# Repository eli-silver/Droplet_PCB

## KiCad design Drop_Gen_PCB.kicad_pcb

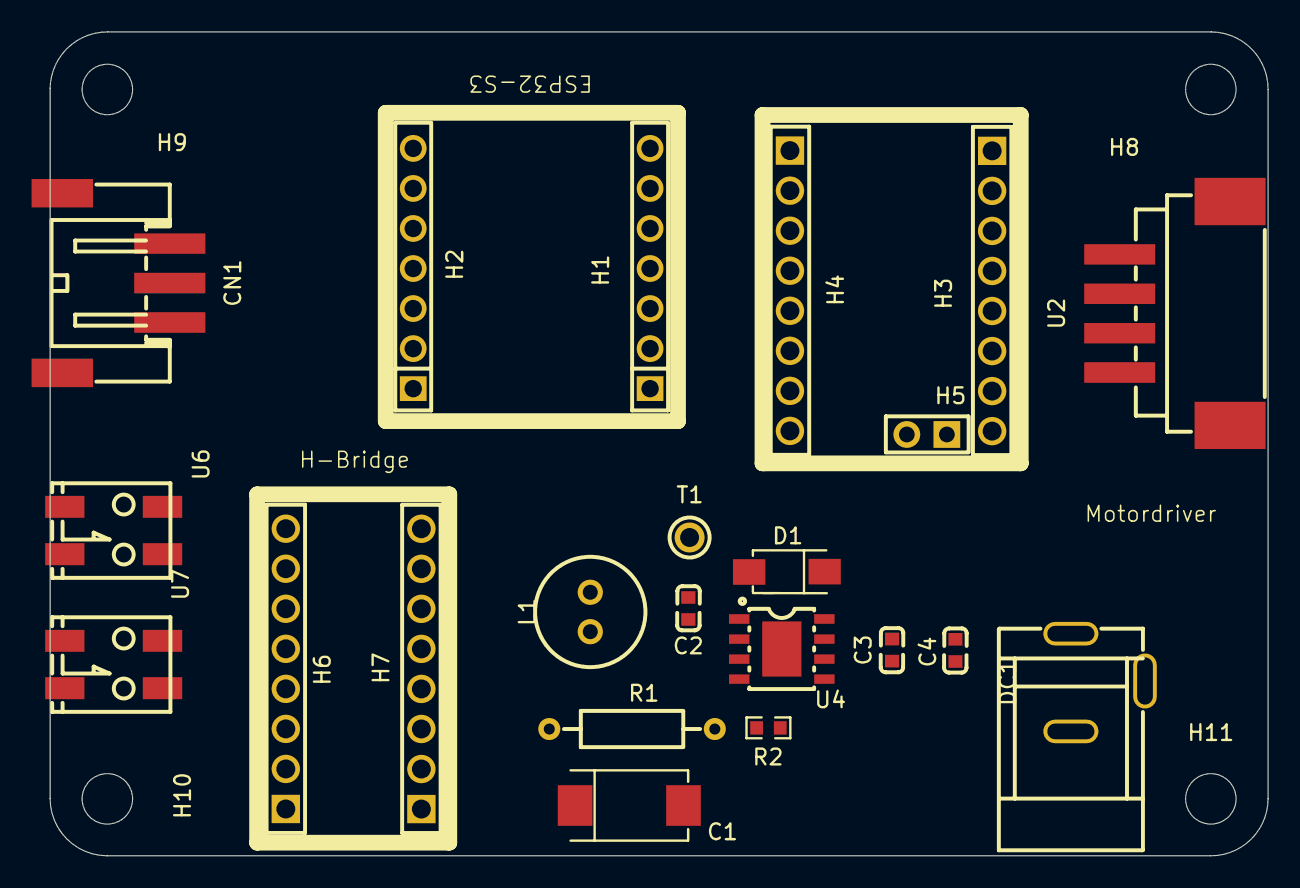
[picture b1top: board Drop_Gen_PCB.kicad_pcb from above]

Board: 2 copper layers, 77.3 x 52.3 mm, 26 parts (0 on the bottom side), 13 nets, no tracks yet.

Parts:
C1: 220uF; CAP-SMD_L7.3-W4.3-FD
C2: 10nF; C0603
C3, C4: 4.7uF; C0603
CN1: S3B-XH-SM4-TB (LF)(SN); CONN-TH_S3B-XH-SM4-TB-LF-SN
D1: B340A_C3018525; SMA_L4.3-W2.6-LS5.0-RD
DC1: Barrel Jack; DC-IN-TH_DC-470-2.1GP
H1, H2: PM254V-11-07-H85; HDR-TH_7P-P2.54-V-F
H3, H4, H6, H7: Header-Female-2.54_1x8; HDR-TH_8P-P2.54-V-F-1
H5: Header-Female-2.54_1x2; HDR-TH_2P-P2.54-V-F
H8, H9, H10, H11: MountingHole; MountingHole_3.2mm_M3
L1: 22uH; IND-TH_BD7.0-P2.50-D0.7
R1: 10KΩ; RES-TH_BD2.3-L6.5-P10.50-D0.5
R2: 3.24kΩ; R0603
T1: test_point; TEST-TH_BD2.54-P1.4_RED
U2: motor_header; CONN-SMD_S4B-XH-SM4-TB-LF-SN
U4: TPS5430DDAR; ESOP-8_L4.9-W3.9-P1.27-LS6.0-TL-EP
U6: Terminal Block Camera; CONN-SMD_2059-302
U7: TB Piezo; CONN-SMD_2059-302

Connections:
+5V: C1.1, H1.7, H3.2, H3.8, H4.7, H6.1, L1.1, R1.1
+30V: C3.2, C4.2, CN1.3, DC1.1, H7.8, U4.7 (VIN)
/Boot: C2.1, C2.2, D1.1 (K), L1.2, T1.1, U4.1 (BOOT), U4.8 (PH)
/Header: H2.3, H2.4
/Signal: CN1.1, H2.5
GND: C1.2, C3.1, C4.1, CN1.2, D1.2 (A), DC1.2, DC1.3, H1.6, H3.1, H3.7, H4.8, H6.4, H6.5, H7.4, H7.5, R2.2, U4.4 (VSENSE), U4.6 (GND), U4.9 (PowerPAD), U6.1
unnamed: CN1.4, CN1.5
unnamed: H3.3, U2.4
unnamed: H3.4, U2.3
unnamed: H3.5, U2.2
unnamed: H3.6, U2.1
unnamed: R1.2, R2.1
unnamed: U2.5, U2.6

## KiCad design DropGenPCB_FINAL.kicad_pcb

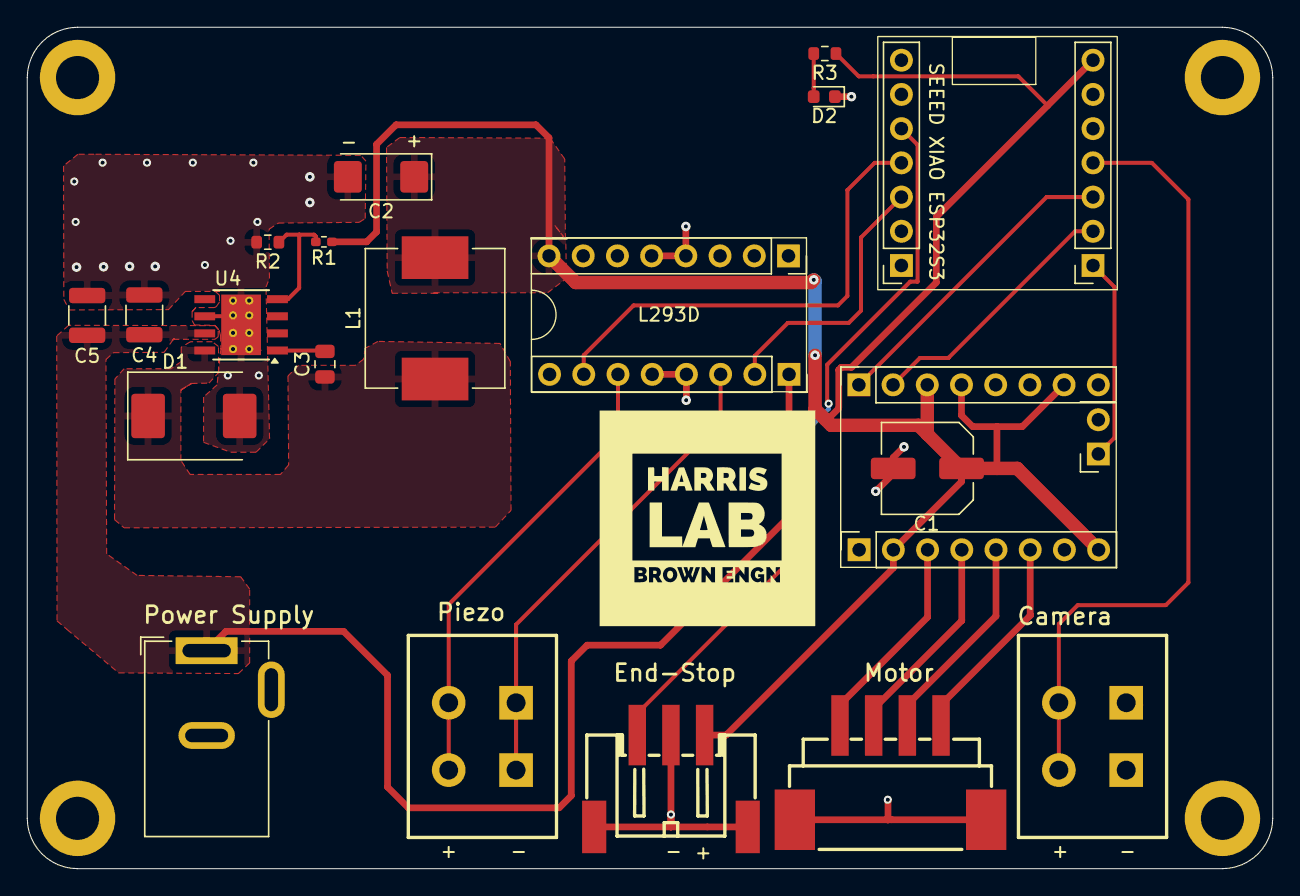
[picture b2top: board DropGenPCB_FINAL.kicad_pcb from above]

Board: 2 copper layers, 92.5 x 62.5 mm, 24 parts (0 on the bottom side), 20 nets.

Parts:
C1: 100uF; C_Elec_6.3x7.7
C2: 220uF; CP_EIA-6032-15_Kemet-U
C3: 10nF; C_0805_2012Metric
C4, C5: 4.7uF; C_1210_3225Metric
D1: B340A_C3018525; D_SMC
D2: LED; LED_0603_1608Metric
H1, H2, H3, H4: MountingHole; MountingHole_3.2mm_M3_DIN965_Pad
J1: JST_3_pin; 3_pin_jst
J2: JST_4_pin; 4_pin_jst
J3: Barrel_Jack_Switch; BarrelJack_GCT_DCJ200-10-A_Horizontal
J4: Camera Terminal Block; terminal_block
J5: Piezo; terminal_block
L1: 22uH; L_Vishay_IHLP-4040
R1: 10KΩ T; R_0402_1005Metric_Pad0.72x0.64mm_HandSolder
R2, R3: 3.24kΩ; R_0603_1608Metric
U1: SEEED XIAO ESP32S3; ESP32S3
U2: TMC2209_SILENTSTEPSTICK; MC2209 numbers
U3: L293D
U4: TPS5430DDAR; TI_SO-PowerPAD-8_ThermalVias

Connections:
+5V: C1.1, C2.1, J1.3, L1.2, R1.1, R3.1, U1.14 (USB/5V), U2.2 (VIO), U2.8 (VM), U2.12 (MS1), U2.15 (UART), U2.16 (PDN), U3.16 (VM)
+30V: C4.2, C5.2, J3.1, U3.8 (VCC), U4.7 (VIN)
/Boot: C3.2, U4.1 (BOOT)
/PH: C3.1, D1.1 (K), L1.1, U4.8 (PH)
/VSENSE: R1.2, R2.1, U4.4 (VSENSE)
DIAG: U1.8 (D7/RX), U2.9 (DIAG)
DIR: U1.10 (D9/MISO), U2.18 (DIR)
GND: C1.2, C2.2, C4.1, C5.1, D1.2 (A), D2.1 (K), H1.1, H2.1, H3.1, H4.1, J1.2, J1.4, J1.5, J2.5, J2.6, J3.2, J3.3, J4.1, R2.2, U1.13 (GND), U2.1 (GND), U2.7 (GND), U2.11 (EN), U2.13 (MS2), U2.14 (SPRD), U3.4 (GND), U3.5 (GND), U3.12 (GND), U3.13 (GND), U4.6 (GND), U4.9 (GNDPAD)
IN3: U1.4 (D3), U3.2 (IN3)
IN4: U1.5 (D4/SDA), U3.7 (IN4)
unnamed: D2.2 (A), R3.2
unnamed: J2.3, U2.5 (M1A)
unnamed: J2.2, U2.4 (M1B)
unnamed: J2.4, U2.6 (M2A)
unnamed: J2.1, U2.3 (M2B)
Piezo 1: J5.1, U3.6 (OUT4)
Piezo 2: J5.2, U3.3 (OUT3)
STEP: U1.9 (D8/SCR), U2.17 (STEP)
Signal: J1.1, U1.3 (D2)
Trigger: J4.2, U1.11 (D10/MOSI)

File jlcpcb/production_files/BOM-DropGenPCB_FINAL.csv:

Comment,Designator,Footprint,LCSC
10nF,C3,C_0805_2012Metric,C128911
JST_3_pin,J1,3_pin_jst,C161860
JST_4_pin,J2,4_pin_jst,C161861
220uF,C2,CP_EIA-6032-15_Kemet-U,C183034
Barrel_Jack_Switch,J3,BarrelJack_GCT_DCJ200-10-A_Horizontal,C194407
LED,D2,LED_0603_1608Metric,C2286
10KΩ T,R1,R_0402_1005Metric_Pad0.72x0.64mm_HandSolder,C25744
4.7uF,"C4,C5",C_1210_3225Metric,C2918502
L293D,U3,L293D,C434590
100uF,C1,C_Elec_6.3x7.7,C72478
Camera Terminal Block,"J4,J5",terminal_block,C784935
3.24kΩ,"R2,R3",R_0603_1608Metric,C844165
22uH ,L1,L_Vishay_IHLP-4040,C845072
B340A_C3018525,D1,D_SMC,C85100
TPS5430DDAR,U4,TI_SO-PowerPAD-8_ThermalVias,C9864
SEEED XIAO ESP32S3,U1,ESP32S3,
TMC2209_SILENTSTEPSTICK,U2,MC2209 numbers,

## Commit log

2024-07-19 Final version sent to JLCPCB
